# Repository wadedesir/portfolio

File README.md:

# Personal Portfolio

**Link to project:** http://desir.dev/

## How It's Made:

**Tech used:** HTML, CSS, JavaScript.

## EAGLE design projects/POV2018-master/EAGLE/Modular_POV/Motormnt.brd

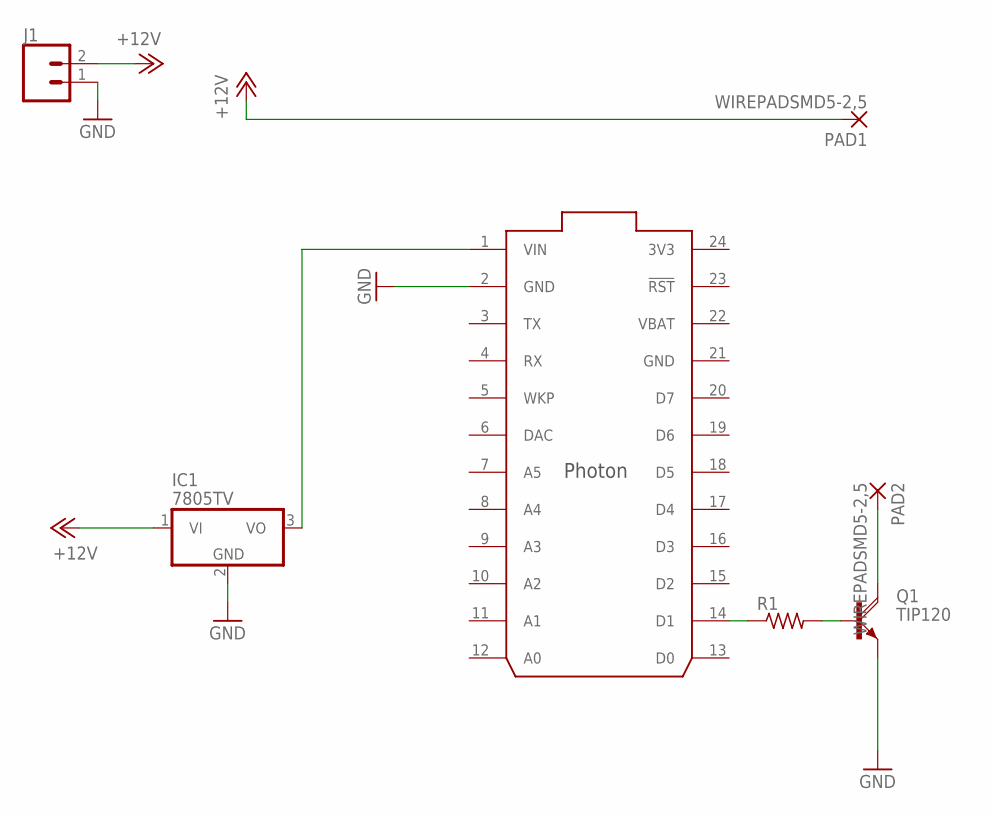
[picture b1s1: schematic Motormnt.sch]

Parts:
IC1: 7805TV; TO220V
J1: CONN_02PTH3; 1X02_LONGPADS
PAD1, PAD2: WIREPADSMD5-2,5; 5-2,5
Q1: TIP120; TO220AH
R1: R-US_0207/7; 0207/7
U$1: PHOTON_WITH_HEADERS; PHOTON

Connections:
3V3: U$1.24 (3V3)
+12V: IC1.1 (VI), J1.2, PAD1.1
GND: IC1.2 (GND), J1.1, Q1.E, U$1.2 (GND), U$1.21 (GND)
unnamed: R1.1, U$1.14 (D1)
unnamed: PAD2.1, Q1.C
unnamed: IC1.3 (VO), U$1.1 (VIN)
unnamed: Q1.B, R1.2
VBAT: U$1.22 (VBAT)

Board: 2 copper layers, 7 parts (2 on the bottom side), 6 nets, no tracks yet.

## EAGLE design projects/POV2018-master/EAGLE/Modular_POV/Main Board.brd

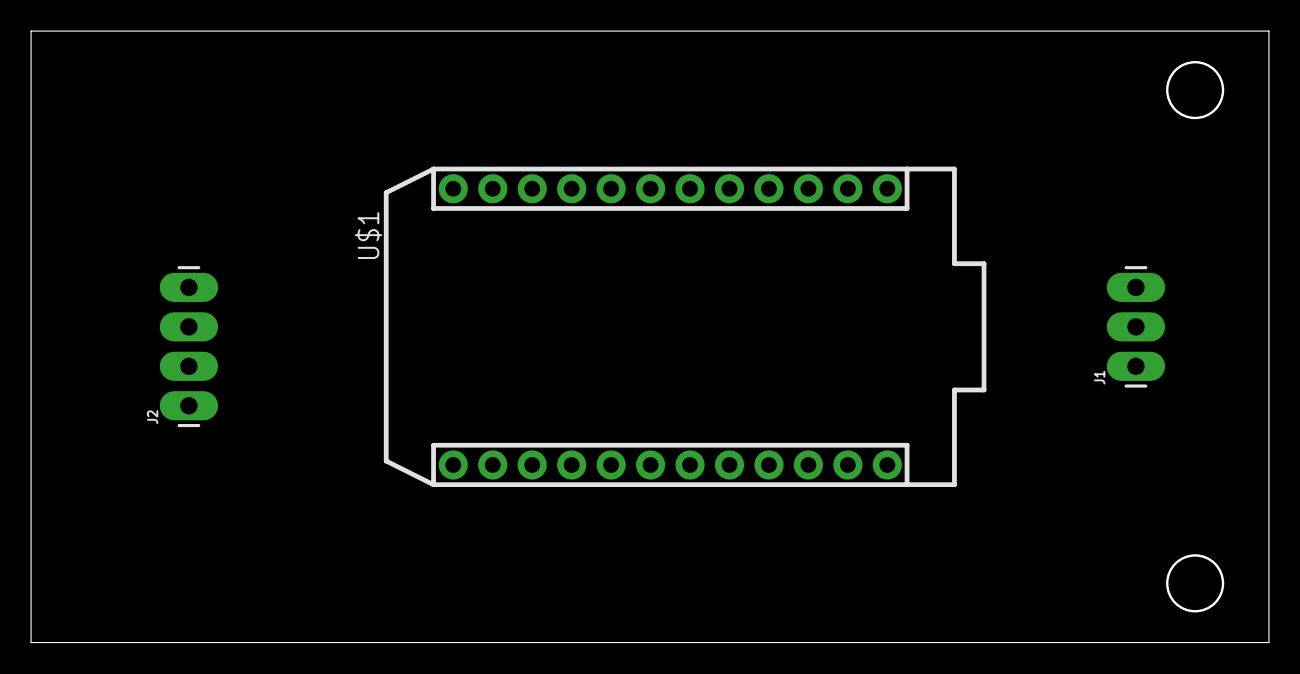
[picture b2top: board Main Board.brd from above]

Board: 2 copper layers, 79.5 x 39.2 mm, 3 parts (0 on the bottom side), 5 nets, no tracks yet.

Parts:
J1: 1X03_LONGPADS
J2: 1X04_LONGPADS
U$1: PHOTON_WITH_HEADERS; PHOTON

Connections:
+5V: J1.3, J2.1, U$1.1
GND: J1.1, J2.4, U$1.2, U$1.21
unnamed: J2.3, U$1.9
unnamed: J2.2, U$1.7
unnamed: J1.2, U$1.14

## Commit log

2021-02-16 template files and readme
2021-02-17 initial html
2021-02-18 Wirefram and external dependencies
2021-02-19 Finished adding content
2021-02-19 added colors to design
2021-02-19 Site fully functional without js
2021-02-19 netlify form
2021-02-19 updating site
2021-02-19 added portfolio img
2021-02-19 social links
2021-02-20 Fixed links and updated portfolio
2021-02-22 centered some stuff
2021-03-08 updated cv link
2021-03-12 new style sheet
2021-03-15 updated profile pic
2021-03-16 landing page
2021-03-16 updated landing image
2021-03-17 working on landing
2021-03-17 remove footer border
2021-03-18 updating landing
2021-03-18 updated pic
2021-03-18 update CSS
2021-03-20 updated author
2021-03-30 folio
2021-03-31 updated head
2021-04-08 moved text
2021-04-08 updated theme and content
2021-04-09 removed lines
2021-04-10 design update
2021-04-10 updated all styles
2021-04-10 files structure
2021-04-10 updating projects
2021-04-11 design all set
2021-04-11 removed POV files
2021-04-11 fixed forms
2021-04-11 removed action
2021-04-11 added action again
2021-04-11 updated form
2021-04-12 email form
2021-04-12 update forms
2021-04-12 action
2021-04-12 forms
2021-04-12 thank you page, links
2021-04-20 links and bio
2021-05-03 added duatone
2021-05-03 removed nasa API
2021-05-12 updated CV
2021-06-27 updated resume
2021-07-16 added nfrg to projects
2021-07-16 updated thumbnails
2021-07-16 updated link styles
2021-07-16 minor syntax updates
2022-02-07 Update issue templates
2022-04-18 switched out portfolio items and made some small text updates to descriptions
2022-05-04 updated cv download link
2022-05-24 created basic gatsby starter for new site
2022-07-26 cleaned up and added c2prog
2022-08-21 added Defense Unicorns and moved portfolio items around
2022-08-21 updated and optimized images & SEO
2022-10-24 Updated Resume and Download Link
2023-01-29 fixed cv link and removed duaton project link
2023-01-31 added g-tag manager
2023-02-08 added time-tracking-dashboard
2023-02-08 updated time tracker
2023-02-16 updated resume download link
2023-02-16 updated favicon
2023-02-16 updated favicon color
2023-02-16 updated resume link
2023-02-16 small updates to resume
2023-02-16 another resume update.
2023-02-22 updated sections with titles and added services section
2023-02-22 cleanup
2023-02-23 added salon hairapy
2023-03-05 updated folder structure and added new images
2023-04-03 Update Resume download link
2023-04-30 added phone number
2023-09-04 Update index.html
    updated resume download link
2024-04-19 added lenoxfit and updated resume download link

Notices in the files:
parts and their libraries:
SparkFun-Connectors: Licensing: Creative Commons ShareAlike 4.0 International - https://creativecommons.org/licenses/by-sa/4.0
